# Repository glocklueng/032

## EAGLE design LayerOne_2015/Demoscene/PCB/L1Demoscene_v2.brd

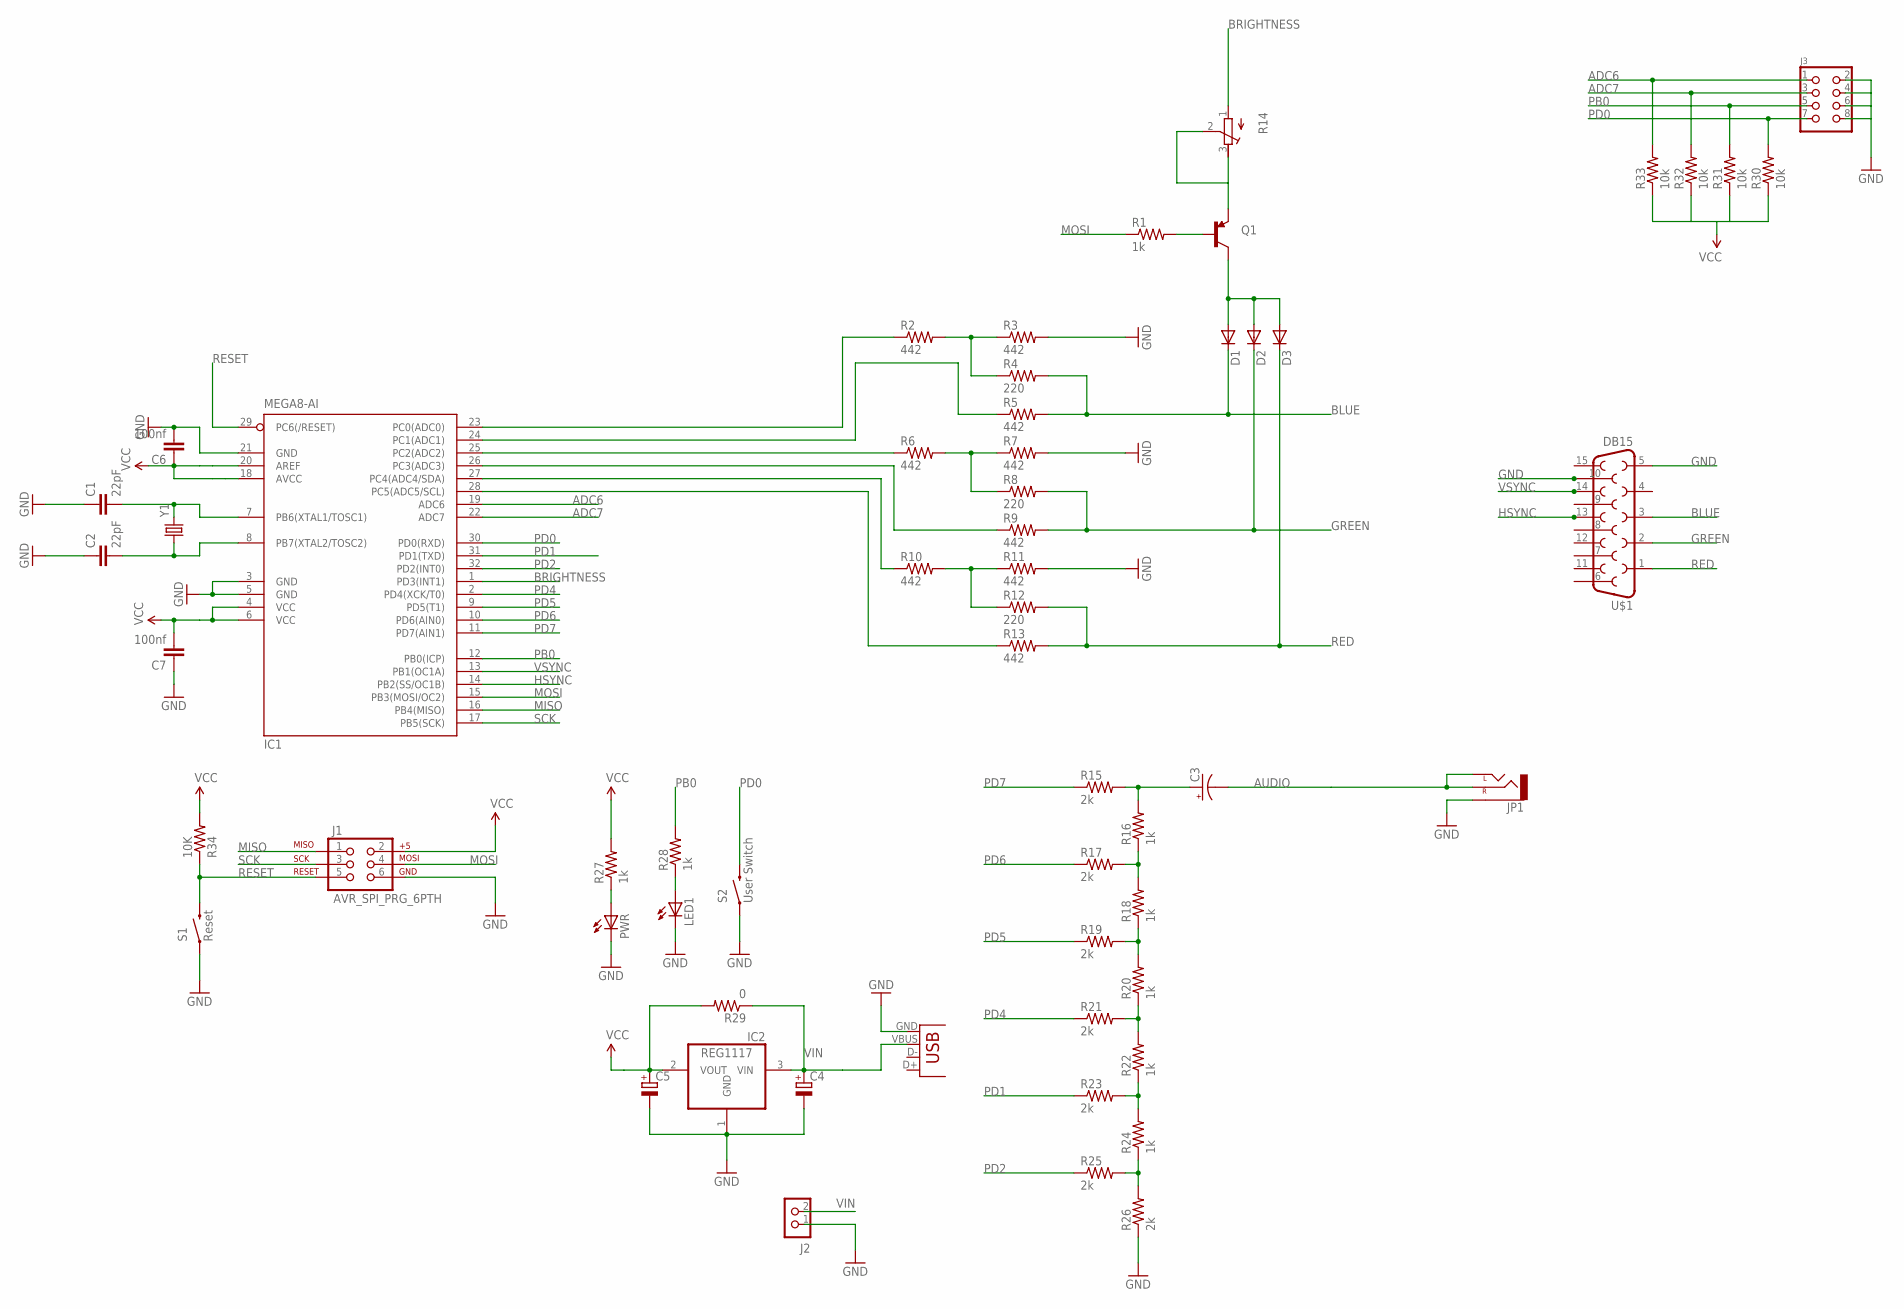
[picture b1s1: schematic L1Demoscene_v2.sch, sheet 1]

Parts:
10K: R34; 0603-RES
C1, C2: 22pF; 0603-CAP
C3: CAP_POL1206; EIA3216
C4, C5: CAPACITOR_POL-SMC_A; SMC_A
C6, C7: 100nf; 0603-CAP
D1, D2, D3: DIODESOD; SOD-323
IC1: MEGA8-AI; TQFP32-08
IC2: REG1117; SOT223
J1: AVR_SPI_PRG_6PTH; 2X3
J2: CON_HEADER_1X02-PTH; M1X2
J3: CON_HEADER_2X04-PTH; M2X4
JP1: AUDIO-JACKPTH; AUDIO-JACK
LED1: LED-0603; LED-603
PWR: LED-0603; LED-603
Q1: TRANSISTOR_PNPSMD; SOT23-3
R1, R16, R18, R20, R22, R24, R27, R28: 1k; 0603-RES
R2, R3, R5, R6, R7, R9, R10, R11, R13: 442; 0603-RES
R4, R8, R12: 220; 0603-RES
R14: R-TRIMM3296W; RTRIM3296W
R15, R17, R19, R21, R23, R25, R26: 2k; 0603-RES
R29: 0; 1206
R30, R31, R32, R33: 10k; 0603-RES
S1: Reset; SPARKFUN-ELECTROMECHANICAL_TACTILE-SWITCH-1101NE
S2: User Switch; SPARKFUN-ELECTROMECHANICAL_TACTILE-SWITCH-1101NE
U$1: DB15
X1: USB-MICROB
Y1: CRYSTALHC49US; HC49US

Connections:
ADC6: IC1.19 (ADC6), J3.1, R33.2
ADC7: IC1.22 (ADC7), J3.3, R32.2
AUDIO: C3.C (-), JP1.RING (RIGHT), JP1.TIP (LEFT)
BLUE: D1.1 (C), R4.2, R5.2, U$1.3
BRIGHTNESS: IC1.1 (PD3(INT1)), R14.1 (A)
GND: C1.1, C2.1, C4.-, C5.-, C6.2, C7.1, IC1.3 (GND), IC1.5 (GND), IC1.21 (GND), IC2.1 (GND), J1.6, J2.1, J3.2, J3.4, J3.6, J3.8, JP1.SLEEVE, LED1.C, PWR.C, R3.2, R7.2, R11.2, R26.1, S1.P$1 (1), S2.P$1 (1), U$1.5, U$1.10, X1.GND
GREEN: D2.1 (C), R8.2, R9.2, U$1.2
HSYNC: IC1.14 (PB2(SS/OC1B)), U$1.13
MISO: IC1.16 (PB4(MISO)), J1.1
MOSI: IC1.15 (PB3(MOSI/OC2)), J1.4, R1.1
unnamed: C1.2, IC1.7 (PB6(XTAL1/TOSC1)), Y1.2
unnamed: C2.2, IC1.8 (PB7(XTAL2/TOSC2)), Y1.1
unnamed: IC1.23 (PC0(ADC0)), R2.1
unnamed: R2.2, R3.1, R4.1
unnamed: D1.2 (A), D2.2 (A), D3.2 (A), Q1.3 (C)
unnamed: Q1.1 (B), R1.2
unnamed: IC1.24 (PC1(ADC1)), R5.1
unnamed: IC1.25 (PC2(ADC2)), R6.1
unnamed: R6.2, R7.1, R8.1
unnamed: PWR.A, R27.1
unnamed: IC1.26 (PC3(ADC3)), R9.1
unnamed: IC1.28 (PC5(ADC5/SCL)), R13.1
unnamed: LED1.A, R28.1
unnamed: IC1.27 (PC4(ADC4/SDA)), R10.1
unnamed: R10.2, R11.1, R12.1
unnamed: Q1.2 (E), R14.2 (S), R14.3 (E)
unnamed: C3.A (+), R15.2, R16.2
unnamed: R16.1, R17.2, R18.2
unnamed: R18.1, R19.2, R20.2
unnamed: R20.1, R21.2, R22.2
unnamed: R22.1, R23.2, R24.2
unnamed: R24.1, R25.2, R26.2
PB0: IC1.12 (PB0(ICP)), J3.5, R28.2, R31.2
PD0: IC1.30 (PD0(RXD)), J3.7, R30.2, S2.P$2 (2)
PD1: IC1.31 (PD1(TXD)), R23.1
PD2: IC1.32 (PD2(INT0)), R25.1
PD4: IC1.2 (PD4(XCK/T0)), R21.1
PD5: IC1.9 (PD5(T1)), R19.1
PD6: IC1.10 (PD6(AIN0)), R17.1
PD7: IC1.11 (PD7(AIN1)), R15.1
RED: D3.1 (C), R12.2, R13.2, U$1.1
RESET: 10K.1, IC1.29 (PC6(/RESET)), J1.5, S1.P$2 (2)
SCK: IC1.17 (PB5(SCK)), J1.3
VCC: 10K.2, C5.+, C6.1, C7.2, IC1.4 (VCC), IC1.6 (VCC), IC1.18 (AVCC), IC1.20 (AREF), IC2.2 (VOUT), J1.2, R27.2, R29.2, R30.1, R31.1, R32.1, R33.1
VIN: C4.+, IC2.3 (VIN), J2.2, R29.1, X1.VBUS
VSYNC: IC1.13 (PB1(OC1A)), U$1.14

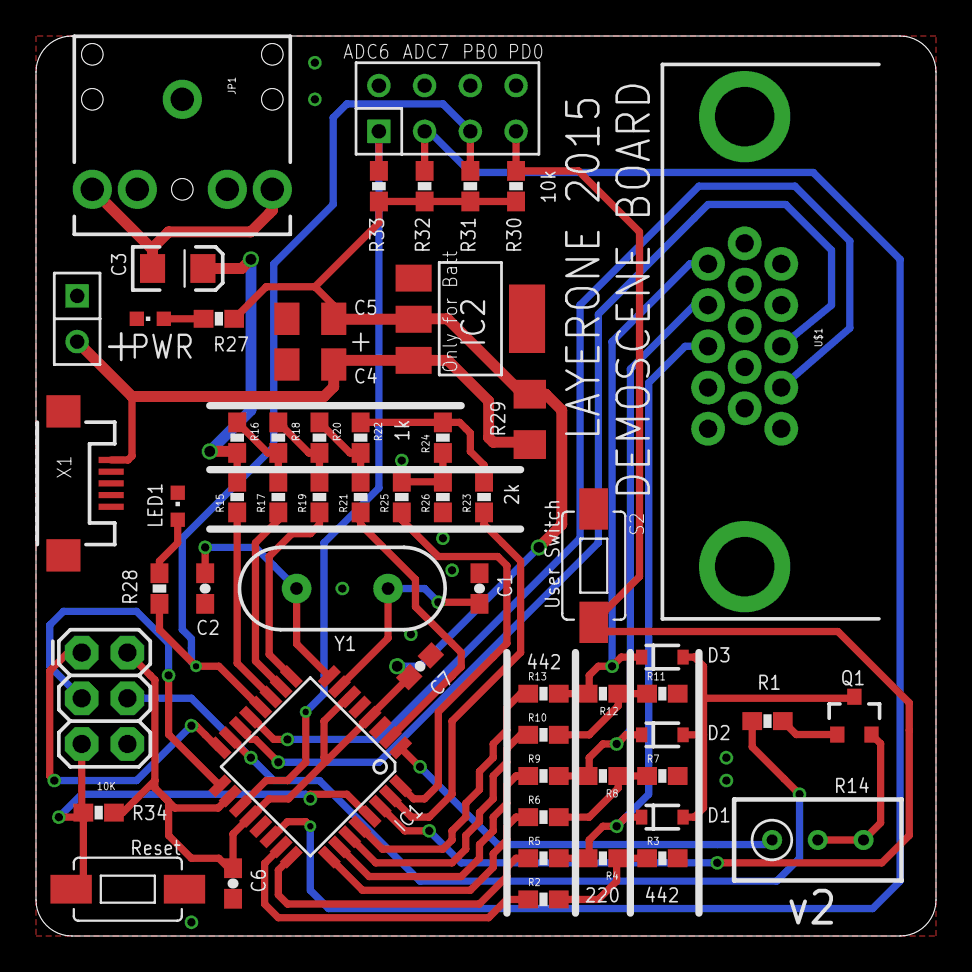
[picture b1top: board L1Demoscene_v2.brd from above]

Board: 2 copper layers, 50.0 x 50.0 mm, 58 parts (0 on the bottom side), 46 nets.

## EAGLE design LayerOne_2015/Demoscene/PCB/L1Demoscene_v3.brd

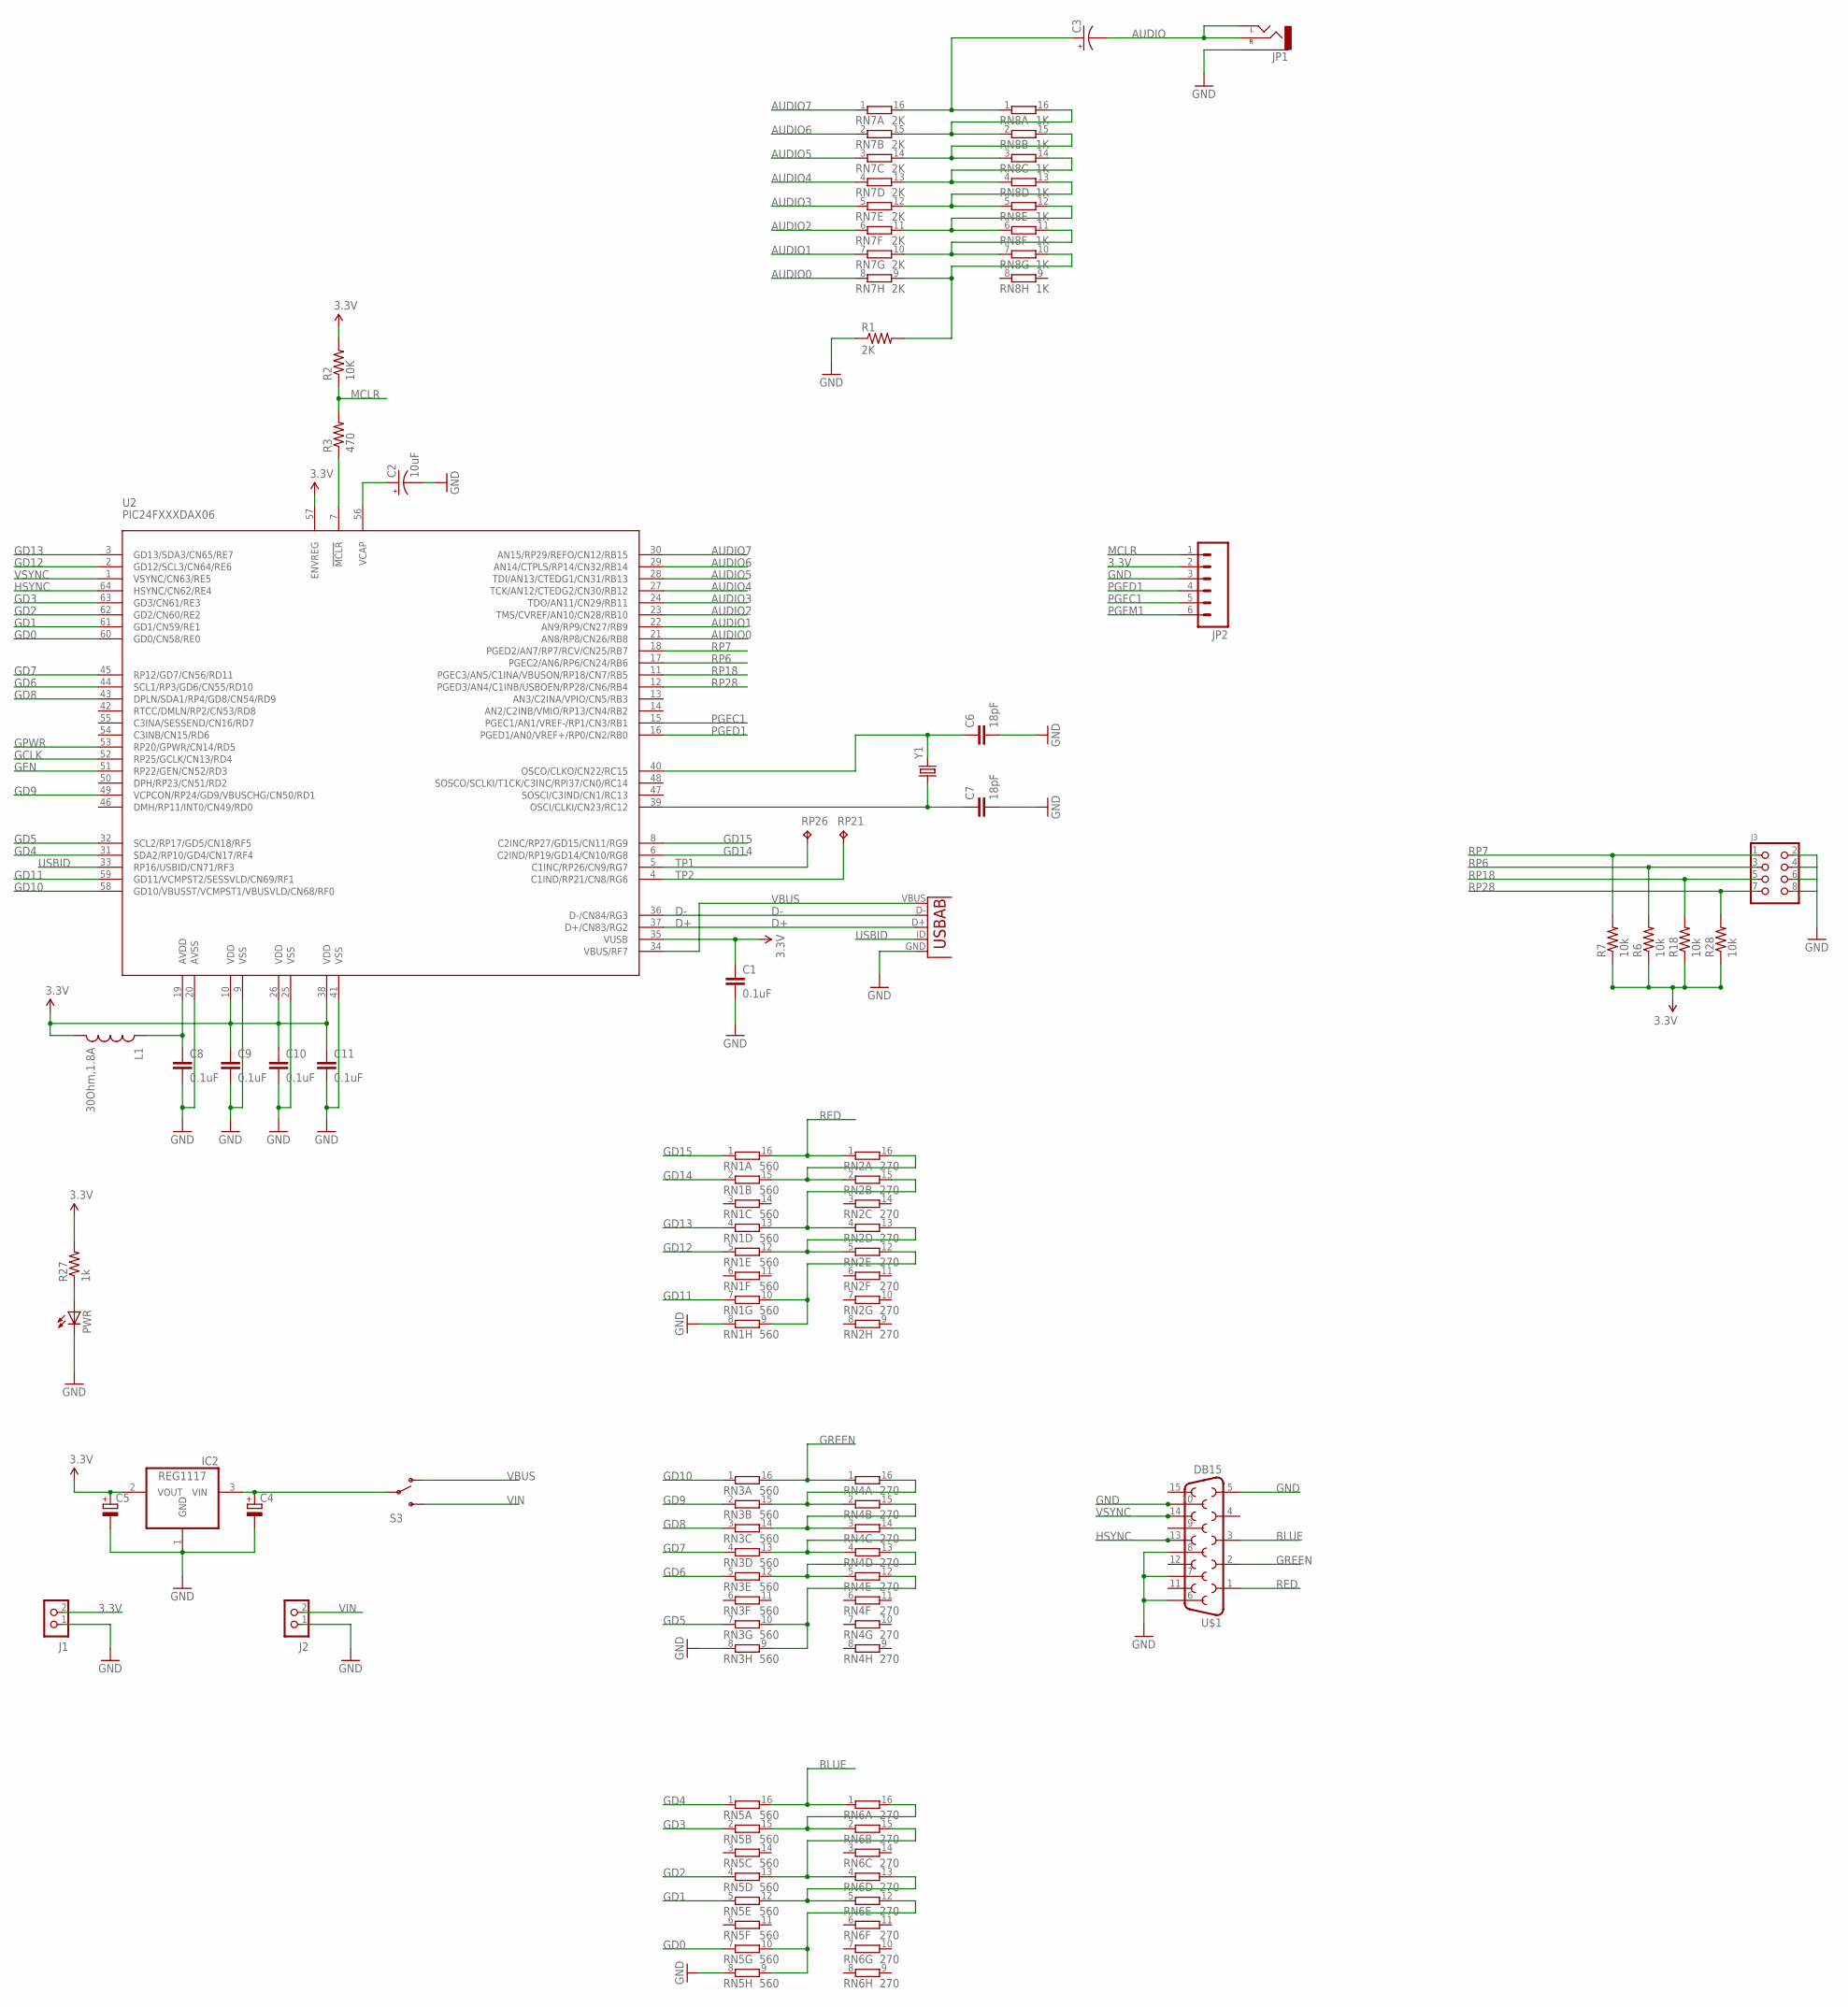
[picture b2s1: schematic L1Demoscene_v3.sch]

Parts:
C1, C8, C9, C10, C11: 0.1uF; 0603-CAP
C2: 10uF; EIA3216
C3: CAP_POL1206; EIA3216
C4, C5: CAPACITOR_POL-SMC_A; SMC_A
C6, C7: 18pF; 0603-CAP
IC2: REG1117; SOT223
J1, J2: CON_HEADER_1X02-PTH; M1X2
J3: CON_HEADER_2X04-PTH; M2X4
JP1: AUDIO-JACKPTH; AUDIO-JACK
JP2: M06SIP; 1X06
L1: 30Ohm,1.8A; C0402
PWR: LED-0603; LED-603
R1: 2K; 0603-RES
R2: 10K; 0603-RES
R3: 470; 0603-RES
R6, R7, R18, R28: 10k; 0603-RES
R27: 1k; 0603-RES
RN1, RN3, RN5: 560; EXB2HV
RN2, RN4, RN6: 270; EXB2HV
RN7: 2K; EXB2HV
RN8: 1K; EXB2HV
RP21, RP26: TPTP06R; TP06R
S3: SWITCH-SPDT-SMD-A; SWITCH-SPST-SMD-A
U2: PIC24FXXXDAX06; PIC24FXXX_TQFP64
U3: USB-AB; USB-AB-MICRO-SMD
U$1: DB15
Y1: CRYSTAL5X3; CRYSTAL-SMD-5X3

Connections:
3.3V: C1.1, C5.+, C9.1, C10.1, C11.1, IC2.2 (VOUT), J1.2, JP2.2, L1.2, R2.2, R6.1, R7.1, R18.1, R27.2, R28.1, U2.10 (VDD), U2.26 (VDD), U2.35 (VUSB), U2.38 (VDD), U2.57 (ENVREG)
AUDIO: C3.C (-), JP1.RING (RIGHT), JP1.TIP (LEFT)
AUDIO0: RN7.8 (1), U2.21 (AN8/RP8/CN26/RB8)
AUDIO1: RN7.7 (1), U2.22 (AN9/RP9/CN27/RB9)
AUDIO2: RN7.6 (1), U2.23 (TMS/CVREF/AN10/CN28/RB10)
AUDIO3: RN7.5 (1), U2.24 (TDO/AN11/CN29/RB11)
AUDIO4: RN7.4 (1), U2.27 (TCK/AN12/CTEDG2/CN30/RB12)
AUDIO5: RN7.3 (1), U2.28 (TDI/AN13/CTEDG1/CN31/RB13)
AUDIO6: RN7.2 (1), U2.29 (AN14/CTPLS/RP14/CN32/RB14)
AUDIO7: RN7.1, U2.30 (AN15/RP29/REFO/CN12/RB15)
BLUE: RN5.16 (2), RN6.1, U$1.3
D+: U2.37 (D+/CN83/RG2), U3.D+
D-: U2.36 (D-/CN84/RG3), U3.D-
GCLK: U2.52 (RP25/GCLK/CN13/RD4)
GD0: RN5.7 (1), U2.60 (GD0/CN58/RE0)
GD1: RN5.5 (1), U2.61 (GD1/CN59/RE1)
GD2: RN5.4 (1), U2.62 (GD2/CN60/RE2)
GD3: RN5.2 (1), U2.63 (GD3/CN61/RE3)
GD4: RN5.1, U2.31 (SDA2/RP10/GD4/CN17/RF4)
GD5: RN3.7 (1), U2.32 (SCL2/RP17/GD5/CN18/RF5)
GD6: RN3.5 (1), U2.44 (SCL1/RP3/GD6/CN55/RD10)
GD7: RN3.4 (1), U2.45 (RP12/GD7/CN56/RD11)
GD8: RN3.3 (1), U2.43 (DPLN/SDA1/RP4/GD8/CN54/RD9)
GD9: RN3.2 (1), U2.49 (VCPCON/RP24/GD9/VBUSCHG/CN50/RD1)
GD10: RN3.1, U2.58 (GD10/VBUSST/VCMPST1/VBUSVLD/CN68/RF0)
GD11: RN1.7 (1), U2.59 (GD11/VCMPST2/SESSVLD/CN69/RF1)
GD12: RN1.5 (1), U2.2 (GD12/SCL3/CN64/RE6)
GD13: RN1.4 (1), U2.3 (GD13/SDA3/CN65/RE7)
GD14: RN1.2 (1), U2.6 (C2IND/RP19/GD14/CN10/RG8)
GD15: RN1.1, U2.8 (C2INC/RP27/GD15/CN11/RG9)
GEN: U2.51 (RP22/GEN/CN52/RD3)
GND: C1.2, C2.C (-), C4.-, C5.-, C6.2, C7.2, C8.2, C9.2, C10.2, C11.2, IC2.1 (GND), J1.1, J2.1, J3.2, J3.4, J3.6, J3.8, JP1.SLEEVE, JP2.3, PWR.C, R1.1, RN1.8 (1), RN3.8 (1), RN5.8 (1), U2.9 (VSS), U2.20 (AVSS), U2.25 (VSS), U2.41 (VSS), U3.GND, U$1.5, U$1.6, U$1.7, U$1.8, U$1.10
GPWR: U2.53 (RP20/GPWR/CN14/RD5)
GREEN: RN3.16 (2), RN4.1, U$1.2
HSYNC: U2.64 (HSYNC/CN62/RE4), U$1.13
MCLR: JP2.1, R2.1, R3.2
unnamed: C8.1, L1.1, U2.19 (AVDD)
unnamed: C3.A (+), RN7.16 (2), RN8.1
unnamed: C7.1, U2.39 (OSCI/CLKI/CN23/RC12), Y1.1
unnamed: R3.1, U2.7 (!MCLR)
unnamed: RN7.15 (2), RN8.2 (1), RN8.16 (2)
unnamed: RN7.14 (2), RN8.3 (1), RN8.15 (2)
unnamed: C4.+, IC2.3 (VIN), S3.2
unnamed: C2.A (+), U2.56 (VCAP)
unnamed: RN7.13 (2), RN8.4 (1), RN8.14 (2)
unnamed: PWR.A, R27.1
unnamed: RN7.12 (2), RN8.5 (1), RN8.13 (2)
unnamed: RN7.11 (2), RN8.6 (1), RN8.12 (2)
unnamed: RN7.10 (2), RN8.7 (1), RN8.11 (2)
unnamed: RN3.15 (2), RN4.2 (1), RN4.16 (2)
unnamed: RN3.14 (2), RN4.3 (1), RN4.15 (2)
unnamed: RN3.13 (2), RN4.4 (1), RN4.14 (2)
unnamed: RN3.12 (2), RN4.5 (1), RN4.13 (2)
unnamed: RN3.9 (2), RN3.10 (2), RN4.12 (2)
unnamed: R1.2, RN7.9 (2), RN8.10 (2)
unnamed: C6.1, U2.40 (OSCO/CLKO/CN22/RC15), Y1.3 (2)
unnamed: RN1.13 (2), RN2.4 (1), RN2.15 (2)
unnamed: RN1.15 (2), RN2.2 (1), RN2.16 (2)
unnamed: RN1.12 (2), RN2.5 (1), RN2.13 (2)
unnamed: RN1.9 (2), RN1.10 (2), RN2.12 (2)
unnamed: RN5.15 (2), RN6.2 (1), RN6.16 (2)
unnamed: RN5.13 (2), RN6.4 (1), RN6.15 (2)
unnamed: RN5.12 (2), RN6.5 (1), RN6.13 (2)
unnamed: RN5.9 (2), RN5.10 (2), RN6.12 (2)
PGEC1: JP2.5, U2.15 (PGEC1/AN1/VREF-/RP1/CN3/RB1)
PGED1: JP2.4, U2.16 (PGED1/AN0/VREF+/RP0/CN2/RB0)
PGEM1: JP2.6
RED: RN1.16 (2), RN2.1, U$1.1
RP6: J3.3, R6.2, U2.17 (PGEC2/AN6/RP6/CN24/RB6)
RP7: J3.1, R7.2, U2.18 (PGED2/AN7/RP7/RCV/CN25/RB7)
RP18: J3.5, R18.2, U2.11 (PGEC3/AN5/C1INA/VBUSON/RP18/CN7/RB5)
RP28: J3.7, R28.2, U2.12 (PGED3/AN4/C1INB/USBOEN/RP28/CN6/RB4)
TP1: RP26.TP, U2.5 (C1INC/RP26/CN9/RG7)
TP2: RP21.TP, U2.4 (C1IND/RP21/CN8/RG6)
USBID: U2.33 (RP16/USBID/CN71/RF3), U3.ID (USBID)
VBUS: S3.1 (O), U2.34 (VBUS/RF7), U3.VBUS
VIN: J2.2, S3.3 (S)
VSYNC: U2.1 (VSYNC/CN63/RE5), U$1.14

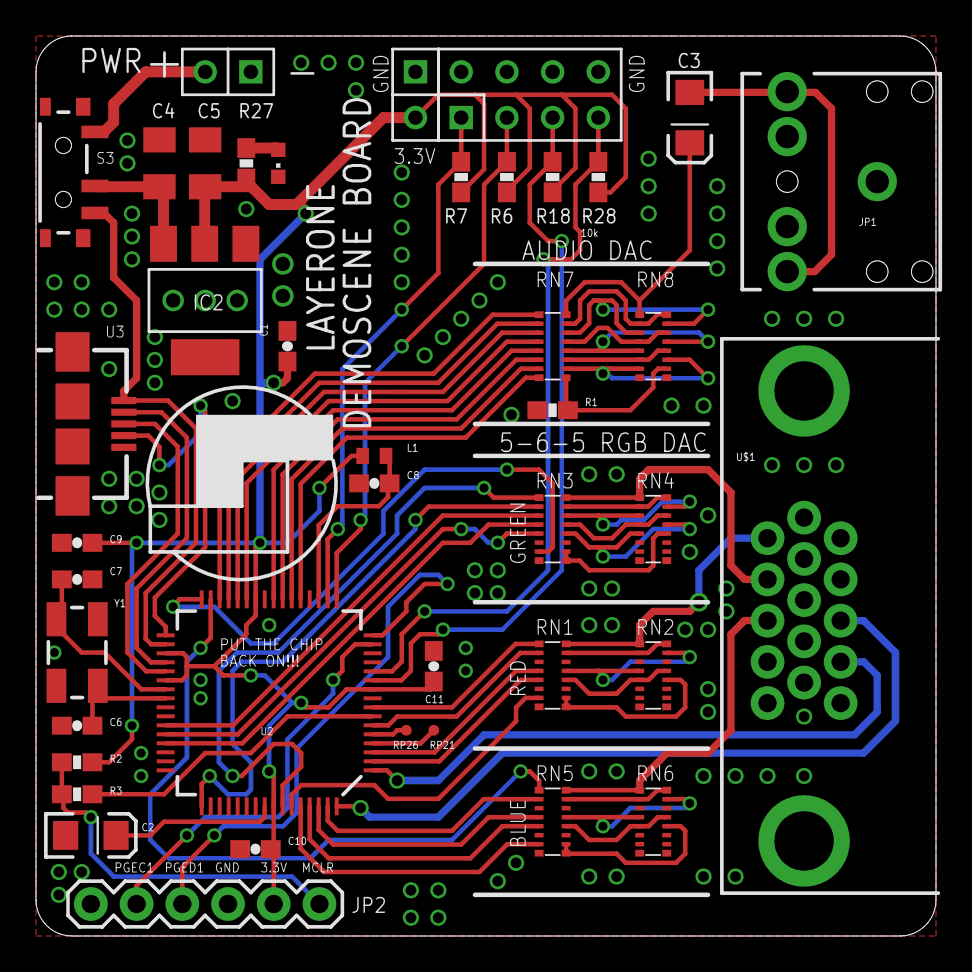
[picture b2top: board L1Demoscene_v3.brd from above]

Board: 2 copper layers, 50.0 x 50.0 mm, 43 parts (0 on the bottom side), 74 nets.

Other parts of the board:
U$2: STM32-PROX_L1LOGO

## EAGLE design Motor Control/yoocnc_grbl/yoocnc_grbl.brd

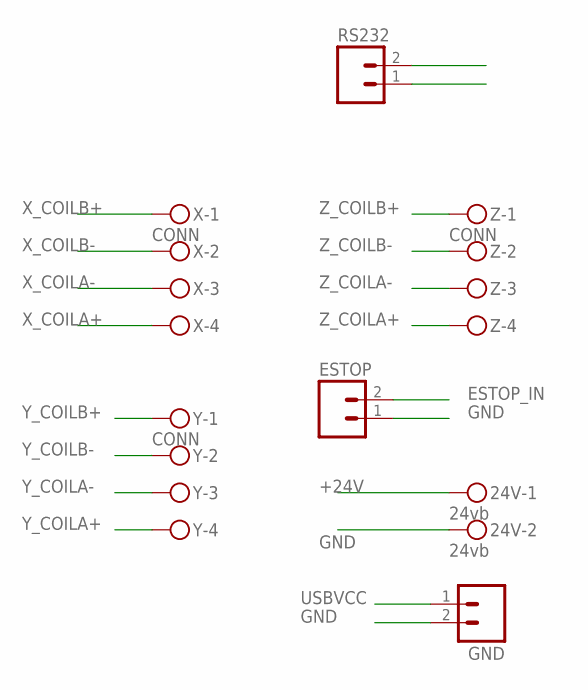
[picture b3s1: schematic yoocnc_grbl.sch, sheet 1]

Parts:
24V: 24vb; MKDSN1,5/2-5,08; PARTNO 0010321021
ESTOP: M02LOCK_LONGPADS; 1X02_LOCK_LONGPADS; PARTNO *
GND: M02LOCK_LONGPADS; 1X02_LOCK_LONGPADS; PARTNO *
RS232: M02LOCK_LONGPADS; 1X02_LOCK_LONGPADS; PARTNO *
X: CONN; MKDSN1,5/4-5,08; PARTNO 0010321041
Y: CONN; MKDSN1,5/4-5,08; PARTNO 0010321041
Z: CONN; MKDSN1,5/4-5,08; PARTNO 0010321041

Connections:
+24V: 24V.1; also elsewhere on the board
ESTOP_IN: ESTOP.2; also elsewhere on the board
GND: 24V.2, ESTOP.1, GND.2; also elsewhere on the board
RXD2: RS232.1; also elsewhere on the board
TXD2: RS232.2; also elsewhere on the board
USBVCC: GND.1; also elsewhere on the board
X_COILA+: X.4; also elsewhere on the board
X_COILA-: X.3; also elsewhere on the board
X_COILB+: X.1; also elsewhere on the board
X_COILB-: X.2; also elsewhere on the board
Y_COILA+: Y.4; also elsewhere on the board
Y_COILA-: Y.3; also elsewhere on the board
Y_COILB+: Y.1; also elsewhere on the board
Y_COILB-: Y.2; also elsewhere on the board
Z_COILA+: Z.4; also elsewhere on the board
Z_COILA-: Z.3; also elsewhere on the board
Z_COILB+: Z.1; also elsewhere on the board
Z_COILB-: Z.2; also elsewhere on the board

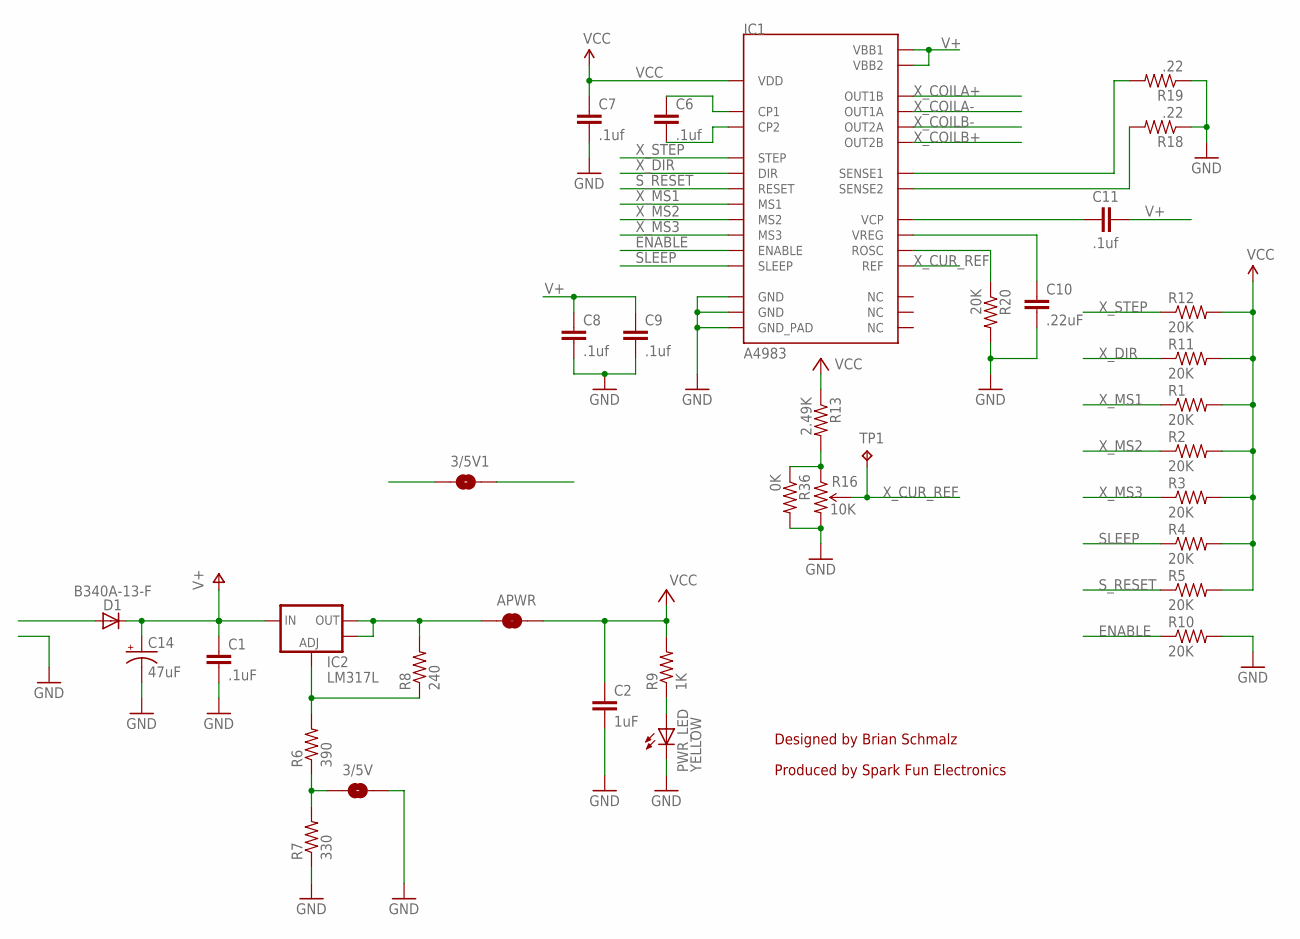
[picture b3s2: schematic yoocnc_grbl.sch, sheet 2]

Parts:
3/5V, 3/5V1: SOLDERJUMPERNO; SJ_2S-NO
APWR: SOLDERJUMPERTRACE; SJ_2S-TRACE
C1: .1uF; 1206; PARTNO LMK105BJ104KV-F
C2: 1uF; 0402-CAP; PARTNO JMK105BJ105KV-F
C6, C7, C8, C9, C11: .1uf; 0402-CAP; PARTNO LMK105BJ104KV-F
C10: .22uF; 0402-CAP; PARTNO C1005Y5V1C224Z
C14: 47uF; PANASONIC_D; PARTNO EEE-FP1V470AP
D1: B340A-13-F; DO-214AC; PARTNO B340A-13-F
IC1: A4983; QFN-28-5MM; PARTNO A4983SETTR-T
IC2: LM317L; SCHMALZHAUS_SOT89; PARTNO LM317LCPK
PWR_LED: YELLOW; LED-0603; PARTNO LY L29K-H1K2-26-Z
R1, R2, R3, R4, R5, R10, R11, R12, R20: 20K; 0402-RES; PARTNO RR0510P-203-D
R6: 390; 0402-RES; PARTNO RR0510P-391-D
R7: 330; 0402-RES; PARTNO RR0510P-331-D
R8: 240; 0402-RES; PARTNO RR0510P-241-D
R9: 1K; 0402-RES; PARTNO RC0402JR-071KL
R13: 2.49K; 0402-RES; PARTNO RC0402FR-072K49L
R16: 10K; 3386U; PARTNO TC33X-2-103E
R18, R19: .22; R2010; PARTNO WSL2010R1100FEA
R36: 0K; 0402-RES; PARTNO RC0402FR-072K49L
TP1: TPPAD1-13; P1-13

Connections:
+24V: D1.A; also elsewhere on the board
ENABLE: IC1.P$2 (ENABLE), R10.1; also elsewhere on the board
GND: 3/5V.2, C1.2, C2.2, C7.2, C8.2, C9.2, C10.2, C14.-, IC1.P$3 (GND), IC1.P$18 (GND), IC1.P$29 (GND_PAD), PWR_LED.C, R7.1, R10.2, R16.3 (CW), R18.1, R19.1, R20.2, R36.2; also elsewhere on the board
unnamed: PWR_LED.A, R9.1
unnamed: R13.2, R16.1 (CCW), R36.1
unnamed: 3/5V.1, R6.1, R7.2
unnamed: IC2.ADJ, R6.2, R8.1
unnamed: C6.1, IC1.P$4 (CP1)
unnamed: C6.2, IC1.P$5 (CP2)
unnamed: IC1.P$13 (ROSC), R20.1
unnamed: C10.1, IC1.P$8 (VREG)
unnamed: C11.1, IC1.P$6 (VCP)
unnamed: IC1.P$27 (SENSE2), R18.2
unnamed: IC1.P$23 (SENSE1), R19.2
SLEEP: IC1.P$14 (SLEEP), R4.1; also elsewhere on the board
S_RESET: IC1.P$12 (RESET), R5.1; also elsewhere on the board
USBVCC: 3/5V1.1; also elsewhere on the board
V+: C1.1, C8.1, C9.1, C11.2, C14.+, D1.C, IC1.P$22 (VBB1), IC1.P$28 (VBB2), IC2.IN; also elsewhere on the board
VCC: 3/5V1.2, APWR.2, C2.1, C7.1, IC1.P$15 (VDD), R1.2, R2.2, R3.2, R4.2, R5.2, R9.2, R11.2, R12.2, R13.1; also elsewhere on the board
X_5V_ALT: APWR.1, IC2.OUT, IC2.OUT@1 (OUT), R8.2
X_COILA+: IC1.P$21 (OUT1B); also elsewhere on the board
X_COILA-: IC1.P$24 (OUT1A); also elsewhere on the board
X_COILB+: IC1.P$1 (OUT2B); also elsewhere on the board
X_COILB-: IC1.P$26 (OUT2A); also elsewhere on the board
X_CUR_REF: IC1.P$17 (REF), R16.2 (WIPER), TP1.TP
X_DIR: IC1.P$19 (DIR), R11.1; also elsewhere on the board
X_MS1: IC1.P$9 (MS1), R1.1; also elsewhere on the board
X_MS2: IC1.P$10 (MS2), R2.1; also elsewhere on the board
X_MS3: IC1.P$11 (MS3), R3.1; also elsewhere on the board
X_STEP: IC1.P$16 (STEP), R12.1; also elsewhere on the board

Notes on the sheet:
Designed by Brian Schmalz
Produced by Spark Fun Electronics

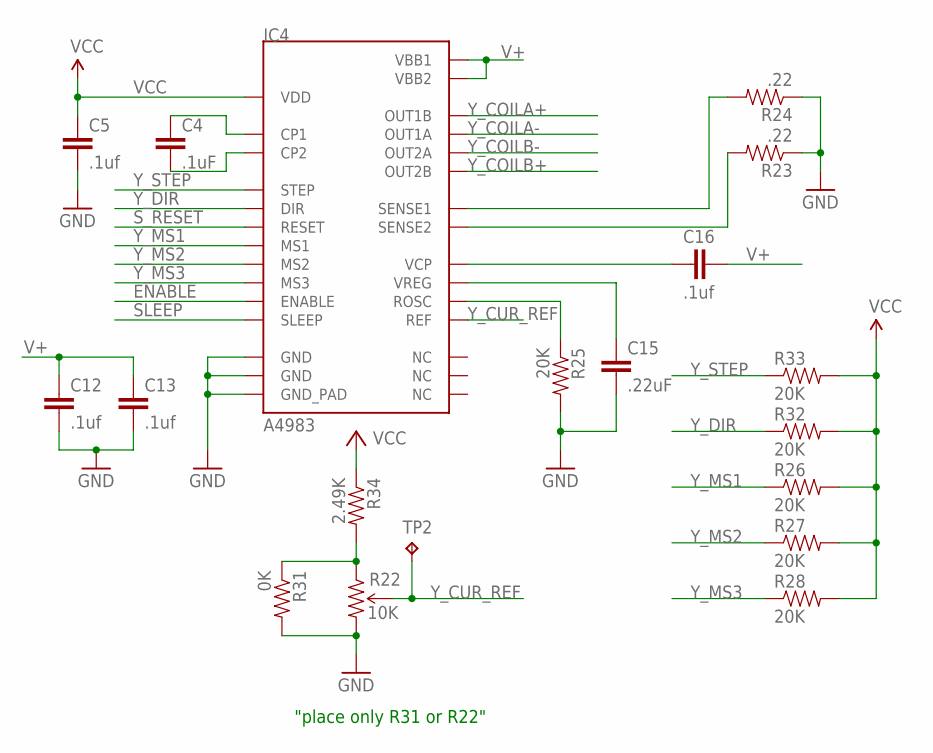
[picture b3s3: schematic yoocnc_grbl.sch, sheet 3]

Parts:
C4: .1uF; 0402-CAP; PARTNO LMK105BJ104KV-F
C5, C12, C13, C16: .1uf; 0402-CAP; PARTNO LMK105BJ104KV-F
C15: .22uF; 0402-CAP; PARTNO C1005Y5V1C224Z
IC4: A4983; QFN-28-5MM; PARTNO A4983SETTR-T
R22: 10K; 3386U; PARTNO TC33X-2-103E
R23, R24: .22; R2010; PARTNO WSL2010R1100FEA
R25, R26, R27, R28, R32, R33: 20K; 0402-RES; PARTNO RR0510P-203-D
R31: 0K; 0402-RES; PARTNO RC0402FR-072K49L
R34: 2.49K; 0402-RES; PARTNO RC0402FR-072K49L
TP2: TPPAD1-13; P1-13

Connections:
ENABLE: IC4.P$2 (ENABLE); also elsewhere on the board
GND: C5.2, C12.2, C13.2, C15.2, IC4.P$3 (GND), IC4.P$18 (GND), IC4.P$29 (GND_PAD), R22.3 (CW), R23.1, R24.1, R25.2, R31.2; also elsewhere on the board
unnamed: IC4.P$27 (SENSE2), R23.2
unnamed: IC4.P$23 (SENSE1), R24.2
unnamed: C4.1, IC4.P$4 (CP1)
unnamed: C4.2, IC4.P$5 (CP2)
unnamed: IC4.P$13 (ROSC), R25.1
unnamed: C15.1, IC4.P$8 (VREG)
unnamed: C16.1, IC4.P$6 (VCP)
unnamed: R22.1 (CCW), R31.1, R34.2
SLEEP: IC4.P$14 (SLEEP); also elsewhere on the board
S_RESET: IC4.P$12 (RESET); also elsewhere on the board
V+: C12.1, C13.1, C16.2, IC4.P$22 (VBB1), IC4.P$28 (VBB2); also elsewhere on the board
VCC: C5.1, IC4.P$15 (VDD), R26.2, R27.2, R28.2, R32.2, R33.2, R34.1; also elsewhere on the board
Y_COILA+: IC4.P$21 (OUT1B); also elsewhere on the board
Y_COILA-: IC4.P$24 (OUT1A); also elsewhere on the board
Y_COILB+: IC4.P$1 (OUT2B); also elsewhere on the board
Y_COILB-: IC4.P$26 (OUT2A); also elsewhere on the board
Y_CUR_REF: IC4.P$17 (REF), R22.2 (WIPER), TP2.TP
Y_DIR: IC4.P$19 (DIR), R32.1; also elsewhere on the board
Y_MS1: IC4.P$9 (MS1), R26.1; also elsewhere on the board
Y_MS2: IC4.P$10 (MS2), R27.1; also elsewhere on the board
Y_MS3: IC4.P$11 (MS3), R28.1; also elsewhere on the board
Y_STEP: IC4.P$16 (STEP), R33.1; also elsewhere on the board

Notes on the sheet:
"place only R31 or R22"

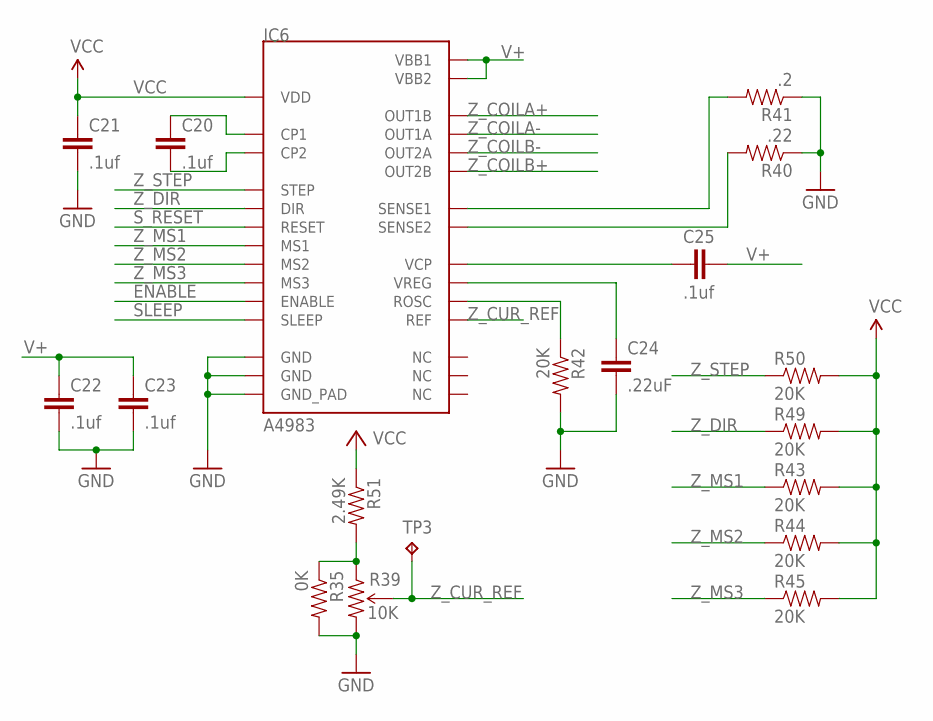
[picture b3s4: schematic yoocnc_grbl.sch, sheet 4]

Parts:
C20, C21, C22, C23, C25: .1uf; 0402-CAP; PARTNO LMK105BJ104KV-F
C24: .22uF; 0402-CAP; PARTNO C1005Y5V1C224Z
IC6: A4983; QFN-28-5MM; PARTNO A4983SETTR-T
R35: 0K; 0402-RES; PARTNO RC0402FR-072K49L
R39: 10K; 3386U; PARTNO TC33X-2-103E
R40: .22; R2010; PARTNO WSL2010R1100FEA
R41: .2; R2010; PARTNO WSL2010R1100FEA
R42, R43, R44, R45, R49, R50: 20K; 0402-RES; PARTNO RR0510P-203-D
R51: 2.49K; 0402-RES; PARTNO RC0402FR-072K49L
TP3: TPPAD1-13; P1-13

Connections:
ENABLE: IC6.P$2 (ENABLE); also elsewhere on the board
GND: C21.2, C22.2, C23.2, C24.2, IC6.P$3 (GND), IC6.P$18 (GND), IC6.P$29 (GND_PAD), R35.2, R39.3 (CW), R40.1, R41.1, R42.2; also elsewhere on the board
unnamed: IC6.P$27 (SENSE2), R40.2
unnamed: IC6.P$23 (SENSE1), R41.2
unnamed: C20.1, IC6.P$4 (CP1)
unnamed: C20.2, IC6.P$5 (CP2)
unnamed: IC6.P$13 (ROSC), R42.1
unnamed: C24.1, IC6.P$8 (VREG)
unnamed: C25.1, IC6.P$6 (VCP)
unnamed: R35.1, R39.1 (CCW), R51.2
SLEEP: IC6.P$14 (SLEEP); also elsewhere on the board
S_RESET: IC6.P$12 (RESET); also elsewhere on the board
V+: C22.1, C23.1, C25.2, IC6.P$22 (VBB1), IC6.P$28 (VBB2); also elsewhere on the board
VCC: C21.1, IC6.P$15 (VDD), R43.2, R44.2, R45.2, R49.2, R50.2, R51.1; also elsewhere on the board
Z_COILA+: IC6.P$21 (OUT1B); also elsewhere on the board
Z_COILA-: IC6.P$24 (OUT1A); also elsewhere on the board
Z_COILB+: IC6.P$1 (OUT2B); also elsewhere on the board
Z_COILB-: IC6.P$26 (OUT2A); also elsewhere on the board
Z_CUR_REF: IC6.P$17 (REF), R39.2 (WIPER), TP3.TP
Z_DIR: IC6.P$19 (DIR), R49.1; also elsewhere on the board
Z_MS1: IC6.P$9 (MS1), R43.1; also elsewhere on the board
Z_MS2: IC6.P$10 (MS2), R44.1; also elsewhere on the board
Z_MS3: IC6.P$11 (MS3), R45.1; also elsewhere on the board
Z_STEP: IC6.P$16 (STEP), R50.1; also elsewhere on the board

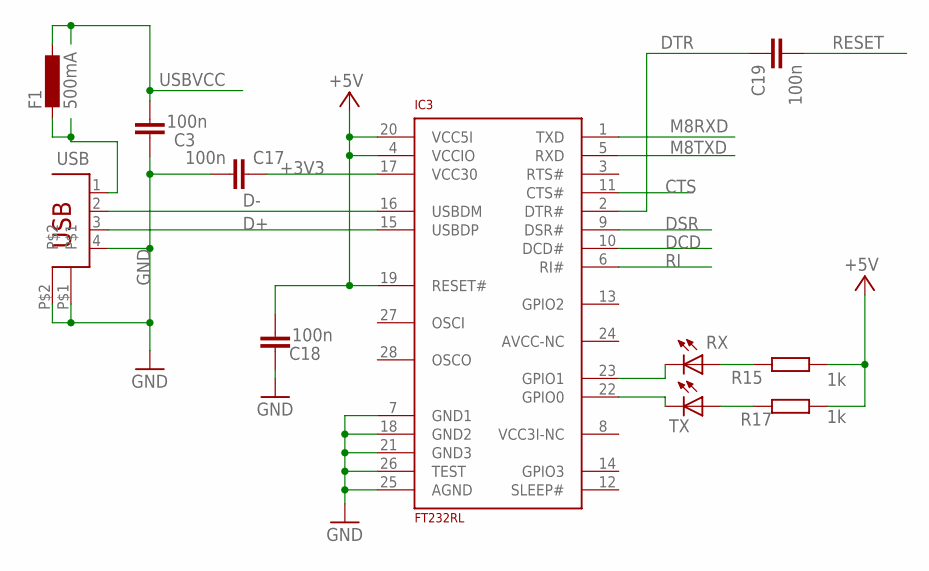
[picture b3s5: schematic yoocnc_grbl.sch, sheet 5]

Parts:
C3, C17, C18, C19: 100n; C0805K; PARTNO CC0805ZRY5V9BB104
F1: 500mA; L1812; PARTNO MINISMDC050F-2
IC3: FT232RL; SSOP28; PARTNO FT232RL-REEL
R15, R17: 1k; R0805W; PARTNO 1623131-1
RX: LEDCHIP-LED0805; CHIP-LED0805; PARTNO LH R974-LP-1
TX: LEDCHIP-LED0805; CHIP-LED0805; PARTNO SML-211DTT86
USB: PN61729; PARTNO 61729-0010BLF

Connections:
+3V3: C17.2, IC3.17 (VCC30)
CTS: IC3.11 (CTS#)
D+: IC3.15 (USBDP), USB.3
D-: IC3.16 (USBDM), USB.2
DCD: IC3.10 (DCD#)
DSR: IC3.9 (DSR#)
DTR: C19.1, IC3.2 (DTR#)
GND: C3.2, C17.1, C18.2, IC3.7 (GND1), IC3.18 (GND2), IC3.21 (GND3), IC3.25 (AGND), IC3.26 (TEST), USB.4, USB.P$1, USB.P$2; also elsewhere on the board
M8RXD: IC3.1 (TXD); also elsewhere on the board
M8TXD: IC3.5 (RXD); also elsewhere on the board
unnamed: IC3.23 (GPIO1), RX.C
unnamed: IC3.22 (GPIO0), TX.C
unnamed: R15.1, RX.A
unnamed: R17.1, TX.A
unnamed: F1.2, USB.1
RESET: C19.2; also elsewhere on the board
RI: IC3.6 (RI#)
USBVCC: C3.1, C18.1, F1.1, IC3.4 (VCCIO), IC3.19 (RESET#), IC3.20 (VCC5I), R15.2, R17.2; also elsewhere on the board

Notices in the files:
Motor Control/yoocnc_grbl/yoocnc_grbl.sch:
licensed under a Creative Commons
parts and their libraries:
SparkFun-FreqCtrl: Licensing: CC v3.0 Share-Alike You are welcome to use this library for commercial purposes.
